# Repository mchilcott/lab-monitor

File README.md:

# Lab Monitoring System

This project contains the firmware for the monitoring nodes used in [Kjaergaard Lab](http://physics.otago.ac.nz/research/kjaergaardlab/), University of Otago, New Zealand. You can view our monitoring dashboard [here](http://hoodoo.otago.ac.nz/mattlab/).

## System Overview

This system uses a collection of sensors connected to ESP8266 and ESP32 boards, programmed with this firmware, modified for the attached sensors as needed. These sensors transmit measurements as text strings (in JSON format) to a MQTT (message queue) server. The measurement messages are then processed by a NodeRED server  which lets us respond live to the data, and also by Telegraf, to pipe the data to an InfluxDB database. The data in the database can then be viewed with Grafana.

The instructions for setting up the services, and sensor modules can be found below. We do not provide complete documentation for each of the tools and services we use, as they are documented.

## Features
- This firmware has drivers for a reasonable number of [sensors](doc/Sensors.md).
- Data collection is using text over MQTT, which makes combining data from other [sources](doc/usb_device_monitor.py) straightforward.
- The network connection of each module is configured via web-browser, so they don't have to be reprogrammed if the wifi changes.
- Each module can be accessed by web-browser, to check it's status, see any error messages, or update the firmware.

## Getting Started (Firmware)
1. To compile and upload this firmware, we use [PlatformIO](https://platformio.org/). PlatformIO is capable of programming many different devices, automatically configureing toolchains and doing much of the hard work of setting a development environment up for you. We recommend most people install PlatformIO along with VSCode by following the instructions [here](https://platformio.org/install/ide?install=vscode).

  > If one has a preference for a different editor, many are supported by PlatformIO, or one can use [PlatformIO Core](https://docs.platformio.org/en/latest/core.html) from the commandline (or makefiles, or configure commands in another IDE). This project can also be compiled from the Arduino IDE, though this is left as an exercise for the reader. (One must take care to follow the Arduino conventions for libraries and file names, and also install the arduino toolchain for ESP8266/ESP32.) We will proceed assuming that you are using VSCode and PlatformIO to program an ESP developement board.

2. Get the code, if you haven't already. You can download a package with all dependencies from the [github releases](https://github.com/mchilcott/lab-monitor/releases).

  > For the most up-to-date version of the code, using git one can run
  > ```
  > git clone --recurse-submodules git://github.com/kjaergaard-lab/lab-monitor.git
  > ```
  > This will fetch the latest verson of our code, as well as the libraries we use for connecting to different sensors, which are loaded as submodules in git 
  >
  > You may also want to generate the code documentation with Doxygen (if installed) using
  > ```
  > doxygen Doxyfile
  > ```

3. Load the code directory into VSCode -- Use `Open Project` from the PlatformIO Home.

4. Copy `src/auth.example.h` to `src/auth.h`. Inside this file, set the username and password used for remote firmware updates. Pick a username and password combination for the firmware update. If you don't use MQTT authentication (this is the default with the server setup below), then these can be left as `nullptr`, which disables MQTT authentication.

5. Open `src/sensor_config.h`. Give the `node_name` variable a meaningful parameter. Each name should be unique to each sensor node, and be meaningful. One can then add a list of monitoring classes. For now, we can start off by setting up a simple analog monitor:

```
const char * node_name = "analog_example_monitor";

std::vector<DCThread *> collectors = {
    new AnalogMonitor ("sensor/example/analog"),
};
```

The parameter here is the MQTT topic to which the data will be posted. One can think of this as the monitored signal's name.

The `AnalogMonitor` class allows other parameters. The full list can be seen in `MonitorThreads.h` or in the generated documentation at `doc/generated/html/classAnalogMonitor.html`

If we were measuring an analog signal that corresponded to a resistance with a ratio of 1 mV/ohm, which we wanted to measure once every 0.5 seconds (500 milliseconds), we could set up the measurement
```
std::vector<DCThread *> collectors = {
    new AnalogMonitor (
      "sensor/example/resistance", // Measurement name (topic)
      500,                         // Sample period (milliseconds)
      1000 /* ohms per volt */,    // Scale factor
      0,                           // Offset
      "Ohms"                       // Units
    ),
};
```

The measurements would then be reported in ohms once every half second.

More examples for monitoring other sensors can be found in the files in `src/config_examples/`.

6. Connect the ESP board board to your computer via USB, and upload the firmware. In VSCode, this is done with upload button at the bottom of the screen, or by Terminal -> Run Task (Ctrl+Alt+T), and selecting Platform IO: Upload, and then Platform IO: Upload Filesystem

From the termial, try
```
pio run -e <env> --target upload
pio run -e <env> --target uploadfs
```
where `<env>` is either esp32 or nodemcuv2 depending on if you are programming an ESP32 modules or and ESP826 module

This will compile your firmware, and upload via USB. If the compilation fails, pay attention to the errors, and check your code. If the upload fails, make sure that the board is connected, and that platformIO is using the correct serial port. You may need to ensure you have the USB serial drivers for the development board - [try here](https://www.silabs.com/products/development-tools/software/usb-to-uart-bridge-vcp-drivers). The serial port can be configured in `platformio.ini` -- see the [platformio docs](https://docs.platformio.org/en/latest/projectconf/section_env_upload.html).

7. Take the freshly programmed node to the lab. For the analog example, connect the signal between A0 and GND and supply power. Power can be supplied by the USB connector, into the Vin port (Which will take anything between 4.75V and 10V), or put 3.3 V into one of the the 3V3 pins. (Be careful not to overload the chip if taking the last option.)

8. If you haven't already, set follow the instructions below for getting started with the data collection services. These modules require an MQTT server to send information to for them to start collecting data.

9. On your phone (or other convenient wifi device), look for a WiFi network with the name `Setup-ESP` followed by a sequence of numbers. Connect to this with password `monitornode` and you should be redirected to the configuration page. If the network isn't showing up, then try repowering the controller.

10. From the page that shows up, use the menu (upper right-hand corner) to:
  - Add a new SSID  - Select the network (SSID) your monitoring server is on, and provide the password
  - MQTT Settings - Set the address of the monitoring server you set up in step 8. (Port 1883 is the default for MQTT. Unless you have a different setup, you won't have to change this.) This can either be the IP address of that computer on the network, or the hostname.
  - If you don't find the MQTT Settings in the menu, then please make sure that you have run Upload Filesystem (uploadfs) from PlatformIO

11. Confirm that data is getting sent your monitoring server. The WiFi network you found in 7 should disappear. If the node isn't able to connect to WiFi, or the server, then check that there isn't an issue with your configuration and repeat step 7.

12. Enjoy collecting data. Have a look at the documentation in `doc` and `doc/generated/html/index.html` to get an idea of the capabilities of this system.

## Getting Started (Services)
In our lab, the data collected by the nodes is sent to a MQTT server (mosquitto). From here, data is put in a database (InfluxDB, put there by Telegraf) for visualisation (with Grafana), and made available to an alerting system (NodeRED).

> The firmware expects to publish data to an MQTT server. The rest of the pipeline is flexible, and these measurements can be integrated with an existing system. Telegraf is a useful tool for connecting different data sources (e.g. MQTT) to different data sinks. One can also find libraries for MQTT in many different languages, simplifying developing your own interface.

To set up the services that we use:
0. Install Docker (Community Edition) on the server - You click on your platform [here](https://docs.docker.com/install/#supported-platforms) to get instructions on how to install docker. (While this is open-source software, it is getting increasingly difficult to download and install docker without having to make an account, and even harder to get from their home page to a place where you can find the installer.)

The advantage of Docker, is that it will manage downloading, running and integrating the services.

It may help to erify that docker is installed properly, by running
```
docker run hello-world
```

Note that you may need to prefix this command, and those following with `sudo` if you're running linux, and haven't added yourself to the [docker group](https://docs.docker.com/install/linux/linux-postinstall/#manage-docker-as-a-non-root-user). If you get a "permission denied" type error, try adding `sudo` at the start. You'll probably be prompted to enter your login password. 

1. Install [docker-compose](https://docs.docker.com/compose/install/). This tool is used to automate setting up multiple services together.

2. Copy `telegraf.conf` and `docker-compose.yml` to a directory on your server

3. From this directory, run the command
```
docker-compose up
```

4. If you haven't run any of these services before, take a well-deserved break. Docker will now download all the services (which takes a while) and start them up.

5. Point your web browser at `http://<server>:3000` to get access to Grafana, whiere you can start to build queries, `http://<server>:8888` to get access to Chronograf, which lets you configure the database,
or `http://<server>:1880` to get access to NodeRED and start to build automation flows.

For more information on playing with these services, see `doc/service-guide.md`.

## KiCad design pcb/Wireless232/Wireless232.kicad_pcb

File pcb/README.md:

# Provided PCBs

Here we provide a coupld of PCB layouts. One for talking to RS232 devices, and one for GPIB devices. These are produced in KiCad, which is freely available. Most of the documentation is in the schematics, with a couple of notes about them both here.

## RX/TX pins
For the first revision of these boards, we had issues with the connection of the serial interface to the RX pin specified in the datasheet, as this is connected to serial flash, causing the device to crash if you try to use it. Fortunately, the UART pins on the ESP32 are configurable, and can be moved to different pins.

Both the RS232 and GPIB boards are in use, and should work without much in the way of debugging outside of the code running on the ESP32. Do note however that the hardware handshaking for RS232 has not been tested, but is connected to the default pins in the ESP32 datasheet. We have not needed to use this in practise yet. If in doubt, you can leave R2, R4 on the RS232 board unpopulated, and the odds of any trouble are very small. Especially as most lab hardware doesn't support hardware handshakes on their RS232 interface.

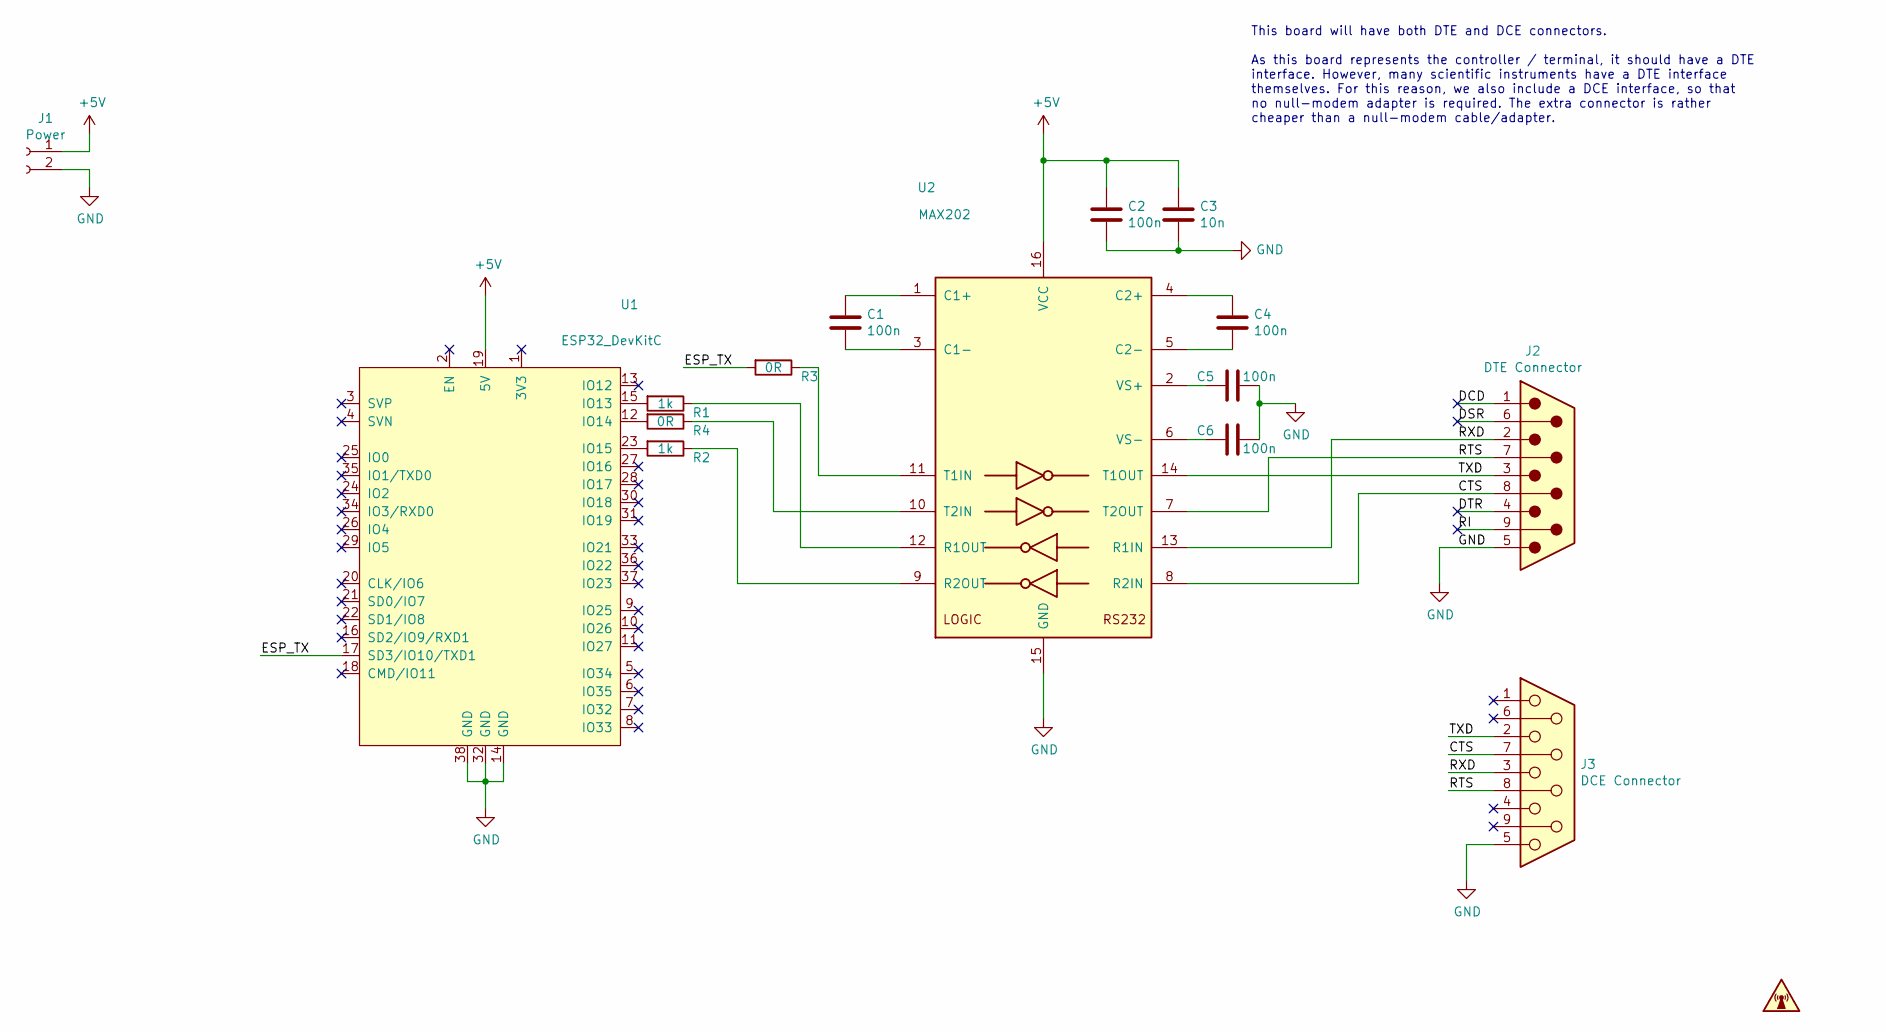
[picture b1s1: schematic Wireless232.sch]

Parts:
C1, C2, C4, C5, C6: 100n; C_1206_3216Metric
C3: 10n; C_1206_3216Metric
J1: Power; PinHeader_1x02_P2.54mm_Vertical
J2: DTE Connector; DSUB-9_Male_Horizontal_P2.77x2.84mm_EdgePinOffset7.70mm_Hou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; Digikey Part AE10968-ND
J3: DCE Connector; DSUB-9_Female_Horizontal_P2.77x2.84mm_EdgePinOffset7.70mm_H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; Digikey Part AE10921-ND
R1, R2: 1k; R_1206_3216Metric
R3, R4: 0R; R_1206_3216Metric
SYM1: Logo; MC
U1: ESP32_DevKitC; ESP32_DevKit_C
U2: MAX202; SOIC-16_3.9x9.9mm_P1.27mm; Digikey Part 296-18480-1-ND

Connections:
+5V: C2.1, C3.1, J1.1, U1.19 (5V), U2.16 (VCC)
/CTS: J2.8, J3.7, U2.8 (R2IN)
/DCD: J2.1
/DSR: J2.6
/DTR: J2.4
/ESP_TX: R3.2, U1.17 (SD3/IO10/TXD1)
/RI: J2.9
/RTS: J2.7, J3.8, U2.7 (T2OUT)
/RXD: J2.2, J3.3, U2.13 (R1IN)
/TXD: J2.3, J3.2, U2.14 (T1OUT)
GND: C2.2, C3.2, C5.1, C6.1, J1.2, J2.5, J3.5, U1.14 (GND), U1.32 (GND), U1.38 (GND), U2.15 (GND)
unnamed: C1.1, U2.1 (C1+)
unnamed: C1.2, U2.3 (C1-)
unnamed: C4.1, U2.4 (C2+)
unnamed: C4.2, U2.5 (C2-)
unnamed: C5.2, U2.2 (VS+)
unnamed: C6.2, U2.6 (VS-)
unnamed: R1.1, U2.12 (R1OUT)
unnamed: R1.2, U1.15 (IO13)
unnamed: R2.1, U2.9 (R2OUT)
unnamed: R2.2, U1.23 (IO15)
unnamed: R3.1, U2.11 (T1IN)
unnamed: R4.1, U2.10 (T2IN)
unnamed: R4.2, U1.12 (IO14)

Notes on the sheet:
This board will have both DTE and DCE connectors. As this board represents the controller / terminal, it should have a DTE interface. However, many scientific instruments have a DTE interface themselves. For this reason, we also include a DCE interface, so that no null-modem adapter is required. Th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

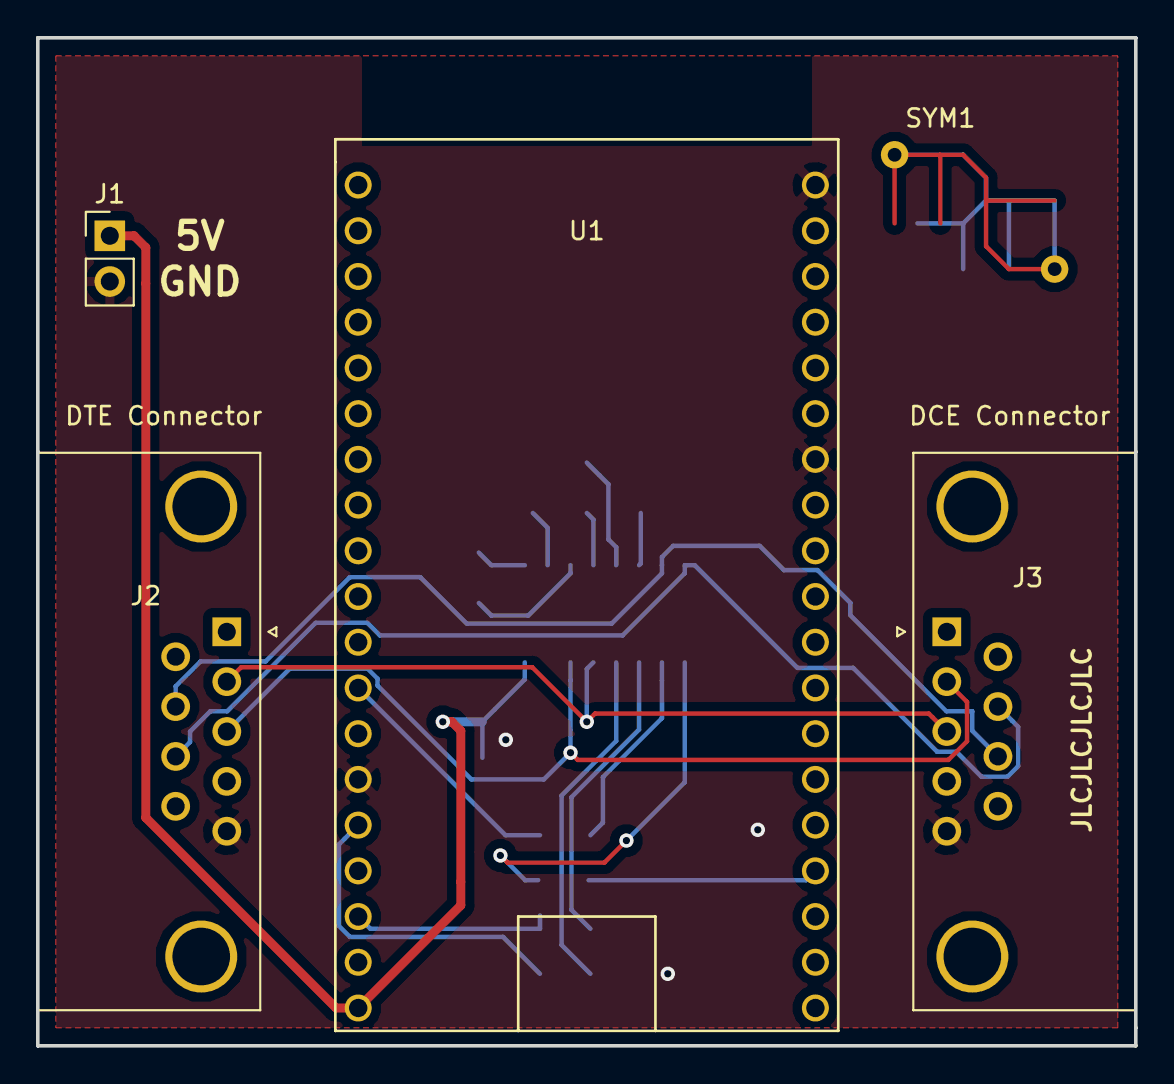
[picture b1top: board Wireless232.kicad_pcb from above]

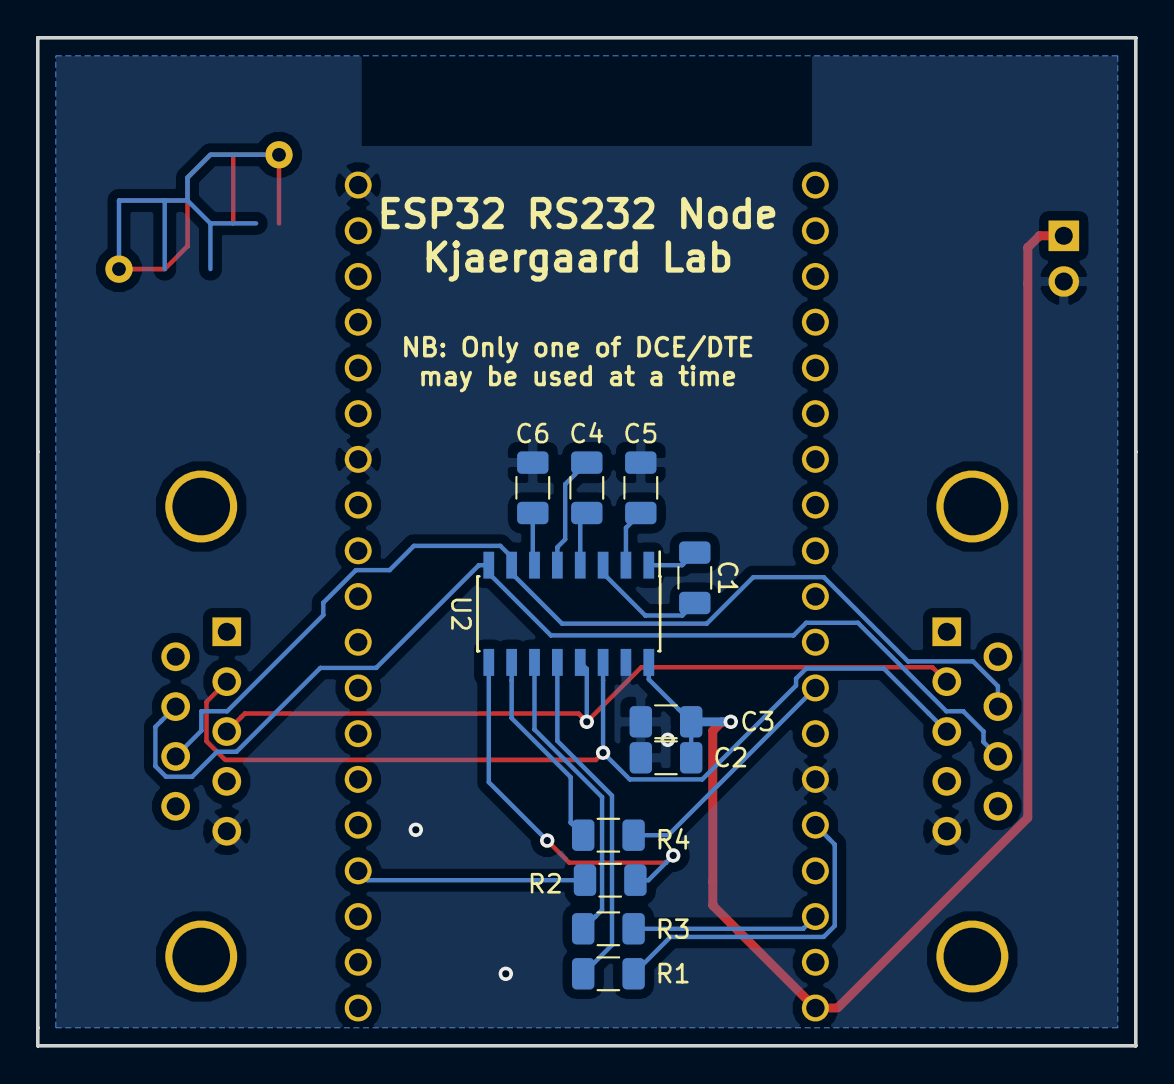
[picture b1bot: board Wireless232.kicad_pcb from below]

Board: 2 copper layers, 61.0 x 56.0 mm, 16 parts (11 on the bottom side), 20 nets.

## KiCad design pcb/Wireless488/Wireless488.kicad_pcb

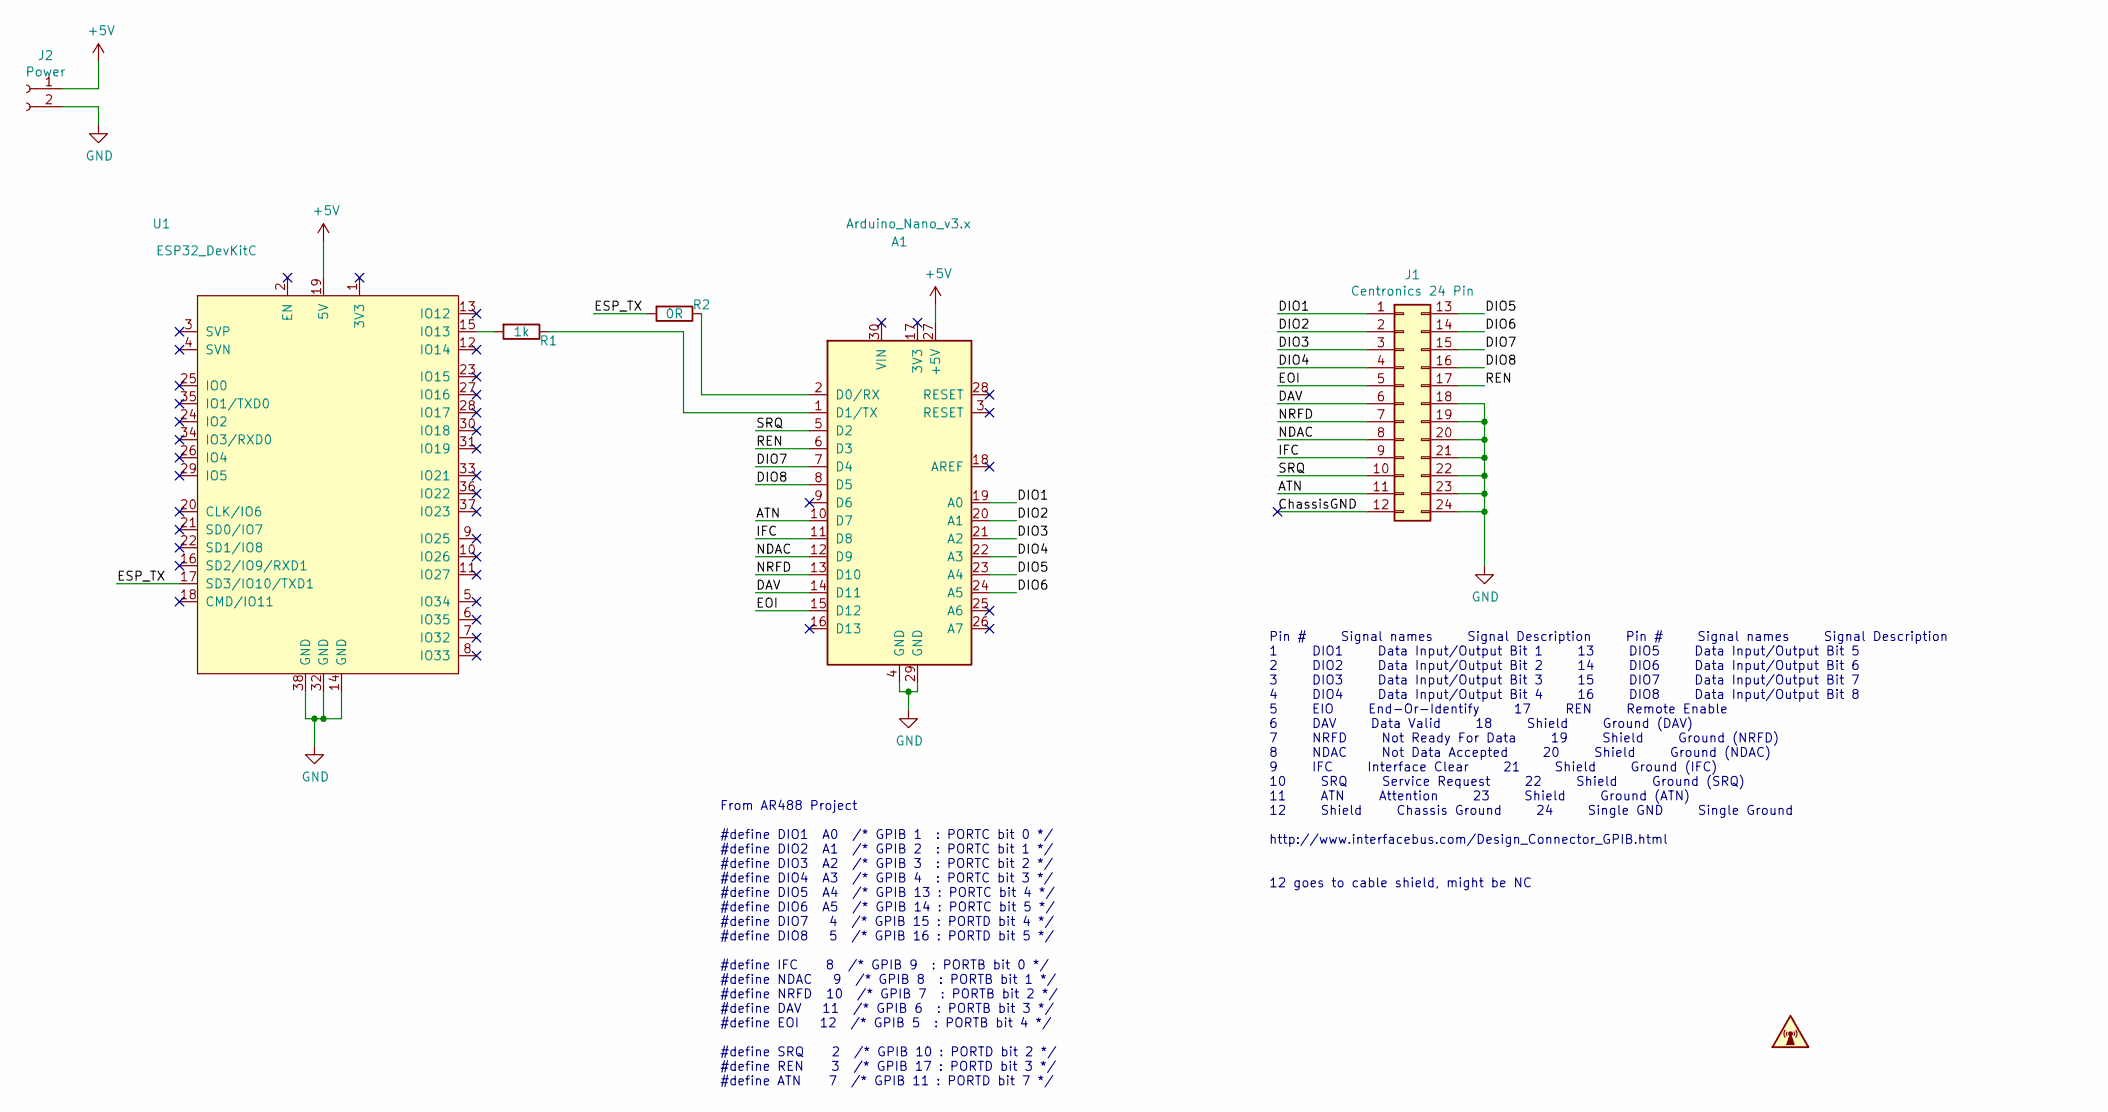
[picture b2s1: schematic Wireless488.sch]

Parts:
A1: Arduino_Nano_v3.x; Arduino_Nano
J1: Centronics 24 Pin; SCSI_Plug_24_RA
J2: Power; PinHeader_1x02_P2.54mm_Vertical
R1: 1k; R_1206_3216Metric
R2: 0R; R_1206_3216Metric
SYM1: Logo; MC
U1: ESP32_DevKitC; ESP32_DevKit_C

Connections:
+5V: A1.27 (+5V), J2.1, U1.19 (5V)
/ATN: A1.10 (D7), J1.11
/ChassisGND: J1.12
/DAV: A1.14 (D11), J1.6
/DIO1: A1.19 (A0), J1.1
/DIO2: A1.20 (A1), J1.2
/DIO3: A1.21 (A2), J1.3
/DIO4: A1.22 (A3), J1.4
/DIO5: A1.23 (A4), J1.13
/DIO6: A1.24 (A5), J1.14
/DIO7: A1.7 (D4), J1.15
/DIO8: A1.8 (D5), J1.16
/EOI: A1.15 (D12), J1.5
/ESP_TX: R2.2, U1.17 (SD3/IO10/TXD1)
/IFC: A1.11 (D8), J1.9
/NDAC: A1.12 (D9), J1.8
/NRFD: A1.13 (D10), J1.7
/REN: A1.6 (D3), J1.17
/SRQ: A1.5 (D2), J1.10
GND: A1.4 (GND), A1.29 (GND), J1.18, J1.19, J1.20, J1.21, J1.22, J1.23, J1.24, J2.2, U1.14 (GND), U1.32 (GND), U1.38 (GND)
unnamed: A1.1 (D1/TX), R1.1
unnamed: A1.2 (D0/RX), R2.1
unnamed: R1.2, U1.15 (IO13)

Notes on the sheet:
Pin # Signal names Signal Description Pin # Signal names Signal Description 1 DIO1 Data Input/Output Bit 1 13 DIO5 Data Input/Output Bit 5 2 DIO2 Data Input/Output Bit 2 14 DIO6 Data Input/Output Bit 6 3 DIO3 Data Input/Output Bit 3 15 DIO7 Data Input/Output Bit 7 4 DIO4 Data Input/Output Bit 4 16 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
From AR488 Project #define DIO1 A0 /* GPIB 1 : PORTC bit 0 */ #define DIO2 A1 /* GPIB 2 : PORTC bit 1 */ #define DIO3 A2 /* GPIB 3 : PORTC bit 2 */ #define DIO4 A3 /* GPIB 4 : PORTC bit 3 */ #define DIO5 A4 /* GPIB 13 : PORTC bit 4 */ #define DIO6 A5 /* GPIB 14 : PORTC bit 5 */ #define DIO7 4 /* GP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

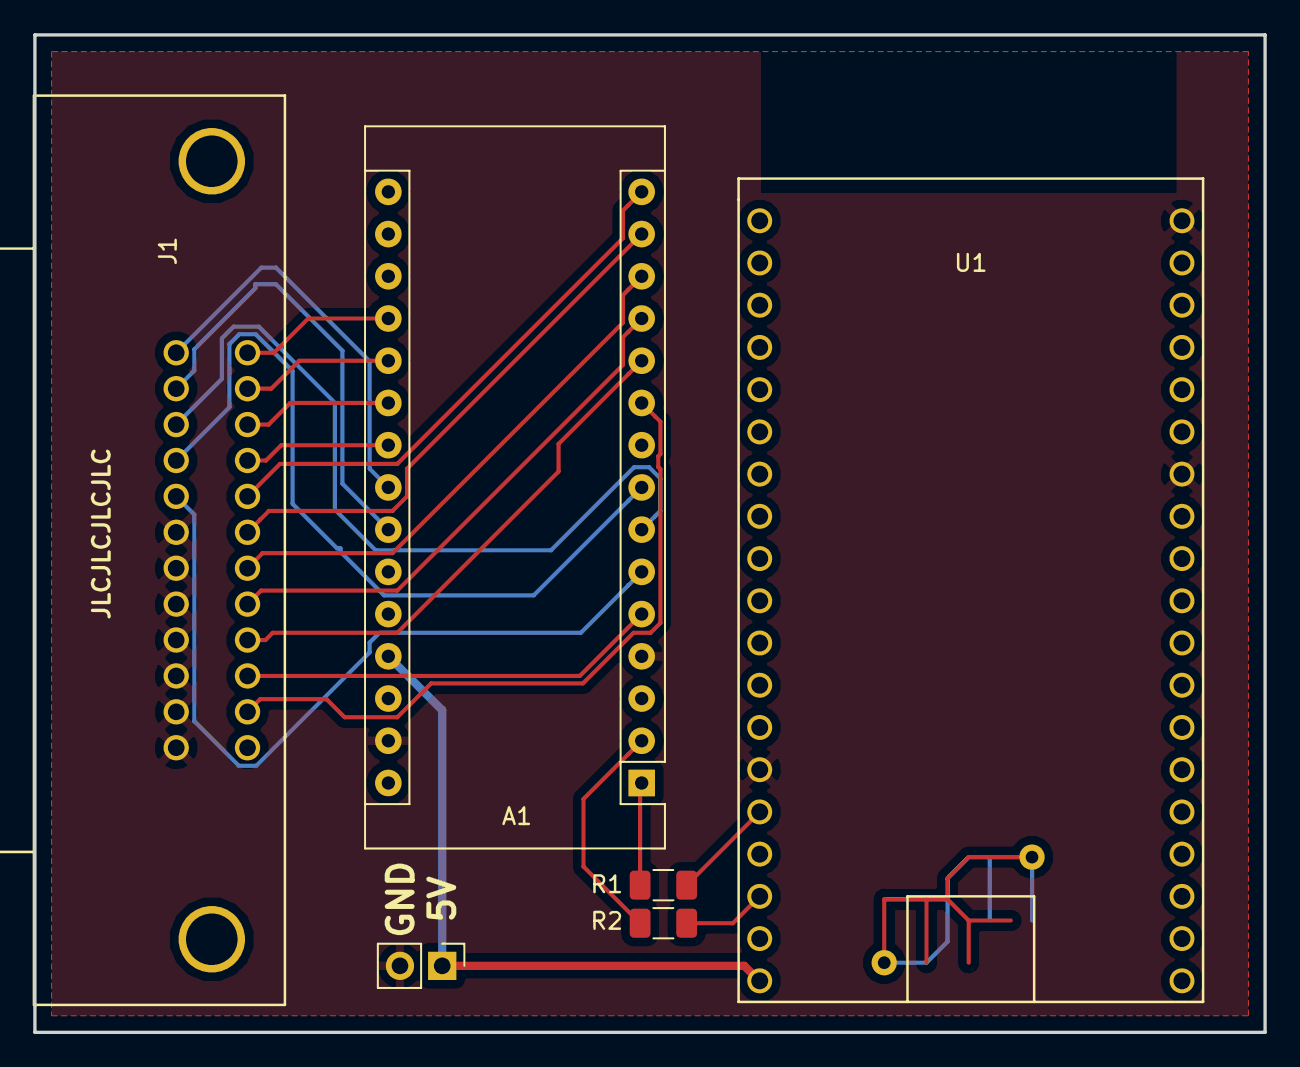
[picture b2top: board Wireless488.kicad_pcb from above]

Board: 2 copper layers, 74.0 x 60.0 mm, 7 parts (1 on the bottom side), 22 nets.

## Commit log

2018-10-23 A working initial version
2018-10-24 Got most sensors back up and running.
2018-10-25 Moved from using "name" key to using topic as an identifier. The entire system is now running this firmware.
2019-04-21 Adding Sensors, and started refactoring threading system
2019-04-22 Updated .gitignore for VS Code
2019-04-23 Temperature sensors and DigitalOutput working
2019-04-23 Added documentation for services and from old lua code, with slight revision
2019-05-10 Inital testing of DigitalMonitor
2019-07-29 In process of refactoring/documenting
2019-07-29 More tidying
2019-07-31 Moved init() to DCThread, plus tidying
2019-08-19 More sensors and documentation
2019-09-03 Changed logging system, and separated out some of the examples.
2019-09-25 Improved documentation slightly.
2019-10-02 Fixed typos
2020-03-26 Moving towards ESP32 Compatibility
2020-03-26 Changed from WiFiManager to AutoConnect
2020-04-10 First revision of ESP32 complete
2020-04-16 Added PCB designs for RS232/GPIB boards
2020-07-07 Included note about config password in README
2020-08-23 PCB Tidy, improved examples for laser monitoring
2020-08-23 Included wavemeter drivers
